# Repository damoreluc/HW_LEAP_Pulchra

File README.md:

# HW_LEAP_Pulchra
File del progetto HW Leap Pulchra

## Scheda della stazione meteo con Arduino MKRWAN1310

__Connettori:__

* X1: direzione vento (X1-1: +3V3; X1-2: tensione analogica tra 0V e +3V3; X1-3: GND)
* X2: anemometro (X2-1: +3V3; X2-2: impulsi, open drain; X2-3: GND)
* X3: alimentazione +3V3 (X3-1: +3V3; X3-2: GND)
* X4: pluviometro (X4-1: +3V3; X4-2: impulsi bilancere, open drain; X4-3 +12V riscaldatore neve; X4-4: GND riscaldatore neve)
* X5: alimentazione +12V (X5-1: +12V; X5-2: GND)
* X6: ventola interna all'armadietto (X6-1: +12V; X6-2: comando PWM ventola, collettore transistor Q1)
* X8: sensore bagnatura foglia (X8-1: +3V3; X8-2: on/off, open drain; X8-3; GND)

---

__Componenti e sensori integrati onboard:__
* U1: scheda microcontrollore e radio MKRWAN1310
* U2: modulo condizionamento per sensore esterno di temperatura PT100, ADAFRUIT_MX31865
* U3: (opzionale) sensore temperatura e umidità interno BME280
* U4: (opzionale) display oled SSD1306_128X64
* U5: (opzionale) sensore di temperatura interna analogico TMP36

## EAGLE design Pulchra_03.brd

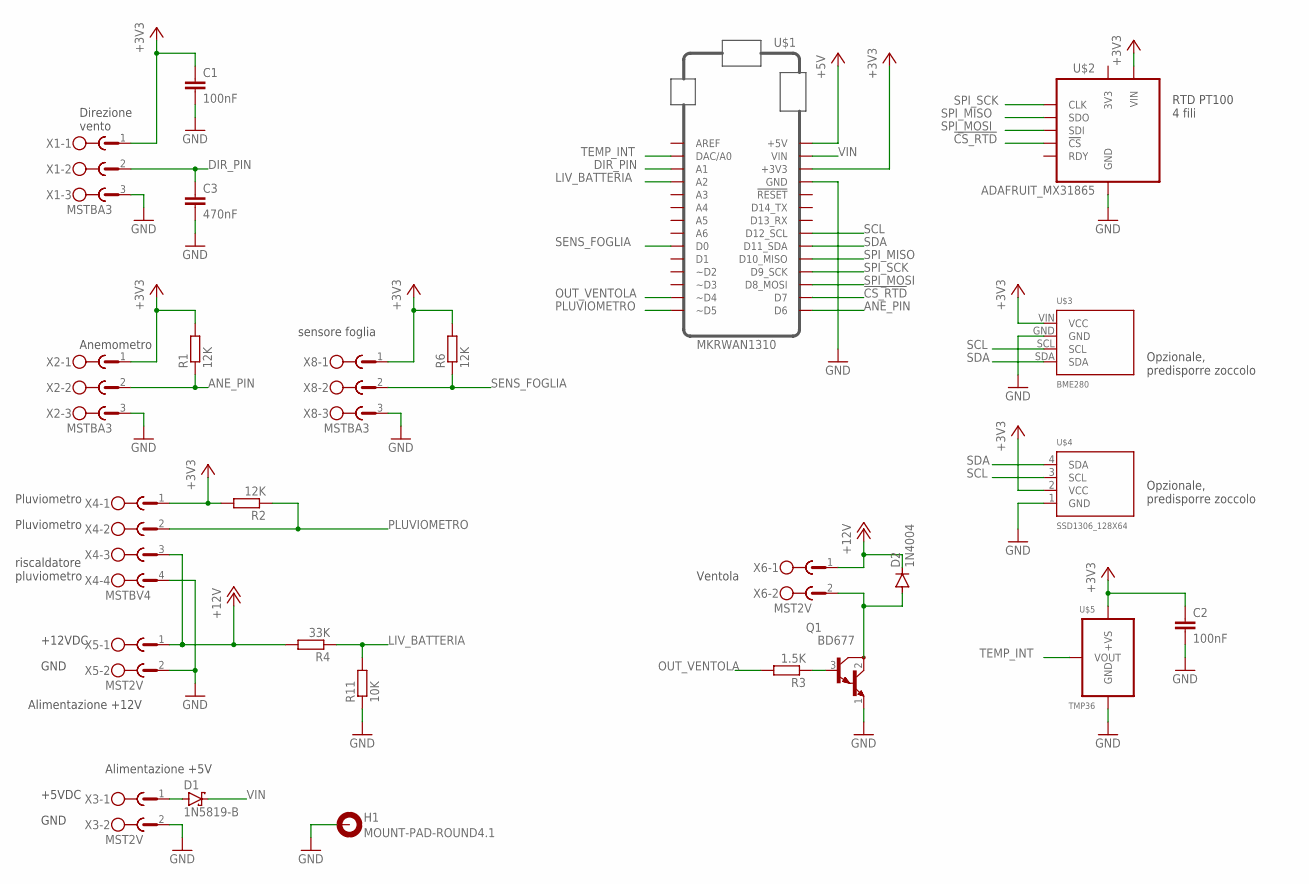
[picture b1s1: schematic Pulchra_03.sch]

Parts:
C1, C2: 100nF; C050-025X075
C3: 470nF; C050-025X075
D1: 1N5819-B; DO41-7.6
D2: 1N4004; DO41-10
H1: MOUNT-PAD-ROUND4.1; 4,1-PAD
Q1: BD677; TO126
R1, R2, R6: 12K; 0207/10
R3: 1.5K; 0207/10
R4: 33K; 0207/10
R11: 10K; 0207/10
U$1: MKRWAN1310
U$2: ADAFRUIT_MX31865; ADAFRUIT_MAX31865
U$3: BME280; BME280_GYBMEP
U$4: SSD1306_128X64; 128X64
U$5: TMP36; TO92
X1, X2, X8: MSTBA3
X3, X5, X6: MST2V; MSTBV2
X4: MSTBV4

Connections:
!CS_RTD!: U$1.D7, U$2.P7 (!CS!)
+3V3: C1.1, C2.1, R1.2, R2.2, R6.2, U$1.+3V3, U$2.P1 (VIN), U$3.VIN (VCC), U$4.2 (VCC), U$5.1 (+VS), X1.1, X2.1, X4.1, X8.1
+5V: U$1.+5V
+12V: D2.C, R4.2, X4.3, X5.1, X6.1
ANE_PIN: R1.1, U$1.D6, X2.2
DIR_PIN: C3.1, U$1.A1, X1.2
GND: C1.2, C2.2, C3.2, H1.B4,1, Q1.1 (E), R11.1, U$1.GND, U$2.P2 (GND), U$3.GND, U$4.1 (GND), U$5.3 (GND), X1.3, X2.3, X3.2, X4.4, X5.2, X8.3
LIV_BATTERIA: R4.1, R11.2, U$1.A2
unnamed: Q1.3 (B), R3.1
unnamed: D1.A, X3.1
unnamed: D2.A, Q1.2 (C), X6.2
OUT_VENTOLA: R3.2, U$1.~D4
PLUVIOMETRO: R2.1, U$1.~D5, X4.2
SCL: U$1.D12_SCL, U$3.SCL, U$4.3 (SCL)
SDA: U$1.D11_SDA, U$3.SDA, U$4.4 (SDA)
SENS_FOGLIA: R6.1, U$1.D0, X8.2
SPI_MISO: U$1.D10_MISO, U$2.P5 (SDO)
SPI_MOSI: U$1.D8_MOSI, U$2.P6 (SDI)
SPI_SCK: U$1.D9_SCK, U$2.P4 (CLK)
TEMP_INT: U$1.DAC0/A0 (DAC/A0), U$5.2 (VOUT)
VIN: D1.C, U$1.VIN

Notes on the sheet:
Opzionale, predisporre zoccolo
Direzione vento
Anemometro
Alimentazione +5V
Pluviometro
Ventola
sensore foglia
Alimentazione +12V
+5VDC
+12VDC
GND
RTD PT100 4 fili
riscaldatore pluviometro

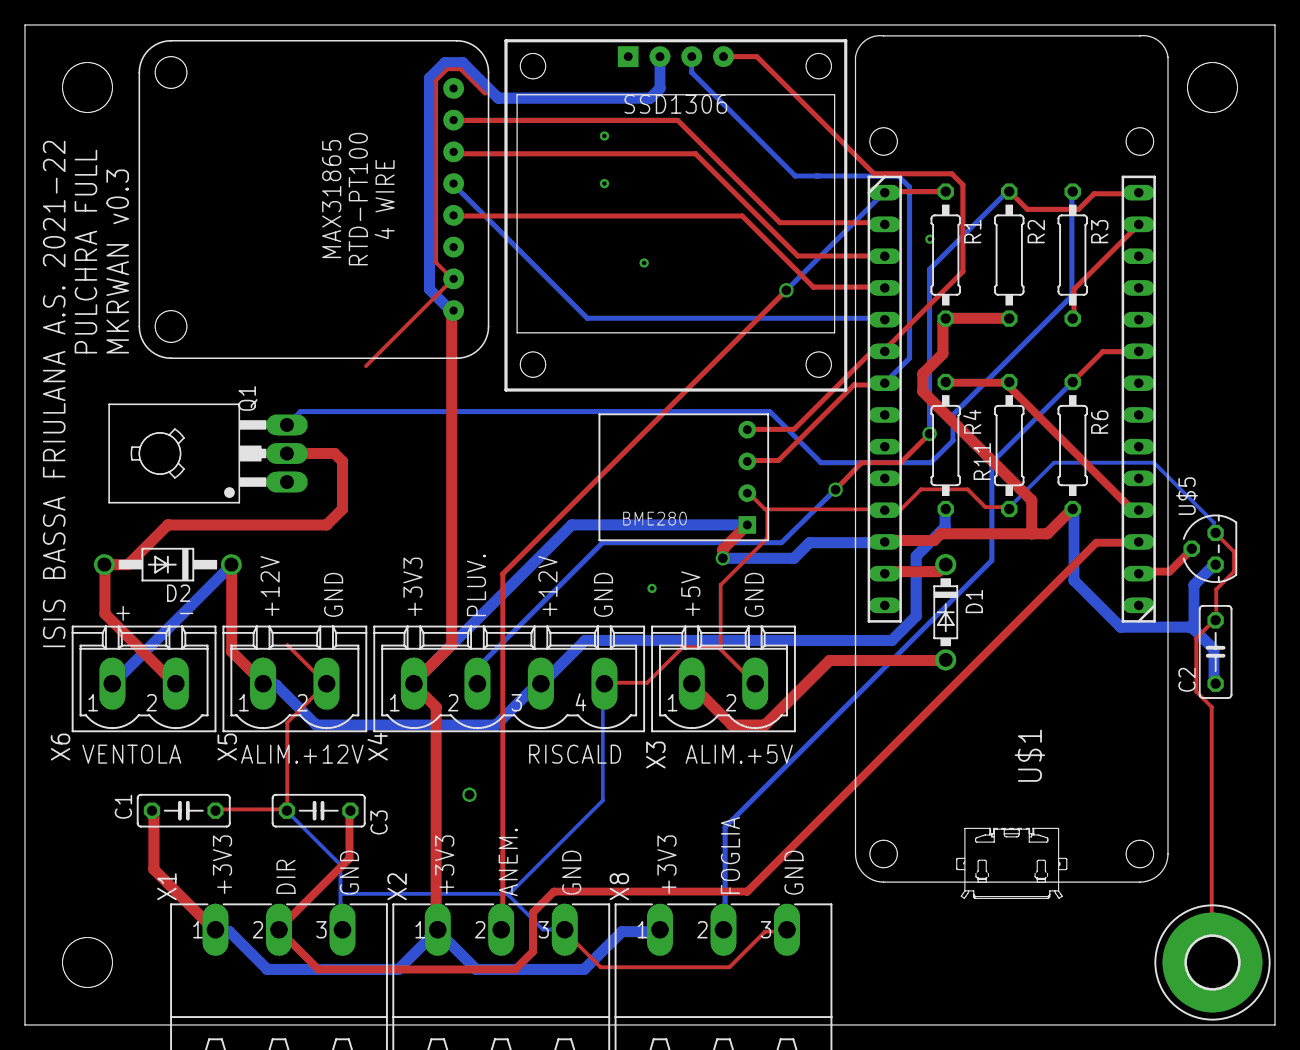
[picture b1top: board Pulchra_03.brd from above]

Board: 2 copper layers, 100.0 x 80.0 mm, 25 parts (0 on the bottom side), 20 nets.

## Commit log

2022-09-26 versione base
2022-10-02 Corretto SSD1306
